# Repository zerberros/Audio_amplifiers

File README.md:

# Audio_amplifiers
Collection of integrated audio amplifiers

## Class-AB 1875 Amplifier

Work in Progress

[LM1875 schematic](Class_AB_LM1875/documentation/LM1875_Amplifier_schem.pdf)

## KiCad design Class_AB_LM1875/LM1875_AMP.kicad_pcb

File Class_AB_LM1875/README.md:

# LM1875_amplifier
audio class-AB amplifier

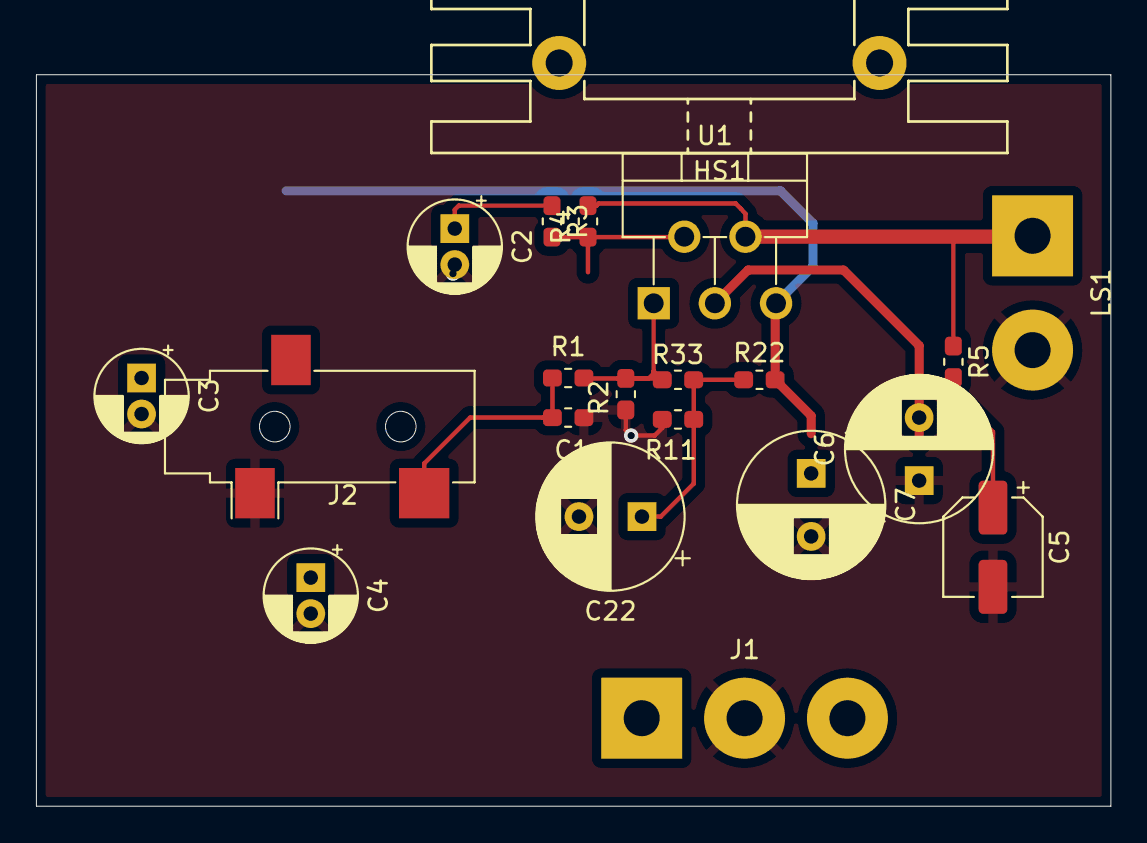
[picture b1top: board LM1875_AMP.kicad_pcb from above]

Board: 2 copper layers, 59.7 x 40.6 mm, 21 parts (0 on the bottom side), 10 nets.

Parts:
C1: 2.2u; C_0603_1608Metric_Pad1.05x0.95mm_HandSolder
C2: 22u; CP_Radial_D5.0mm_P2.00mm
C3, C4: 0.1u; CP_Radial_D5.0mm_P2.00mm
C5: 0.22u; CP_Elec_5x4.5
C6, C7, C22: 100u; CP_Radial_D8.0mm_P3.50mm
HS1: Heatsink; Heatsink_Stonecold_HS-132_32x14mm_2xFixation1.5mm
J1: Conn_01x03; SolderWirePad_1x03_P5.715mm_Drill2mm
J2: AudioJack2_SwitchT; Jack_3.5mm_CUI_SJ-3523-SMT_Horizontal
LS1: Speaker; SolderWirePad_1x02_P7.62mm_Drill2mm
R1: 1Meg; R_0603_1608Metric_Pad1.05x0.95mm_HandSolder
R2, R11, R22, R33: 22k; R_0603_1608Metric_Pad1.05x0.95mm_HandSolder
R3: 1k; R_0603_1608Metric_Pad1.05x0.95mm_HandSolder
R4: 20k; R_0603_1608Metric_Pad1.05x0.95mm_HandSolder
R5: 1; R_0603_1608Metric_Pad1.05x0.95mm_HandSolder
U1: LM1875; TO-220-5_P3.4x3.7mm_StaggerOdd_Lead3.8mm_Vertical

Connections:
GND: C2.2, C3.2, C4.2, C5.2, C6.1, C7.2, C22.2, J1.2, J2.S, LS1.2, R1.2, R2.2, R11.1
unnamed: C1.1, R2.1, R33.2, U1.1
unnamed: C1.2, J2.T, R1.1
unnamed: C2.1, R3.1
unnamed: C5.1, R5.2
unnamed: C22.1, R11.2, R22.2, R33.1
unnamed: LS1.1, R4.1, R5.1, U1.4
unnamed: R3.2, R4.2, U1.2
VCC: C3.1, C7.1, J1.3, R22.1, U1.5
VEE: C4.1, C6.2, J1.1, U1.3

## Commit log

2021-04-11 added LM1875 Amplifier
2021-04-11 Update documentation
